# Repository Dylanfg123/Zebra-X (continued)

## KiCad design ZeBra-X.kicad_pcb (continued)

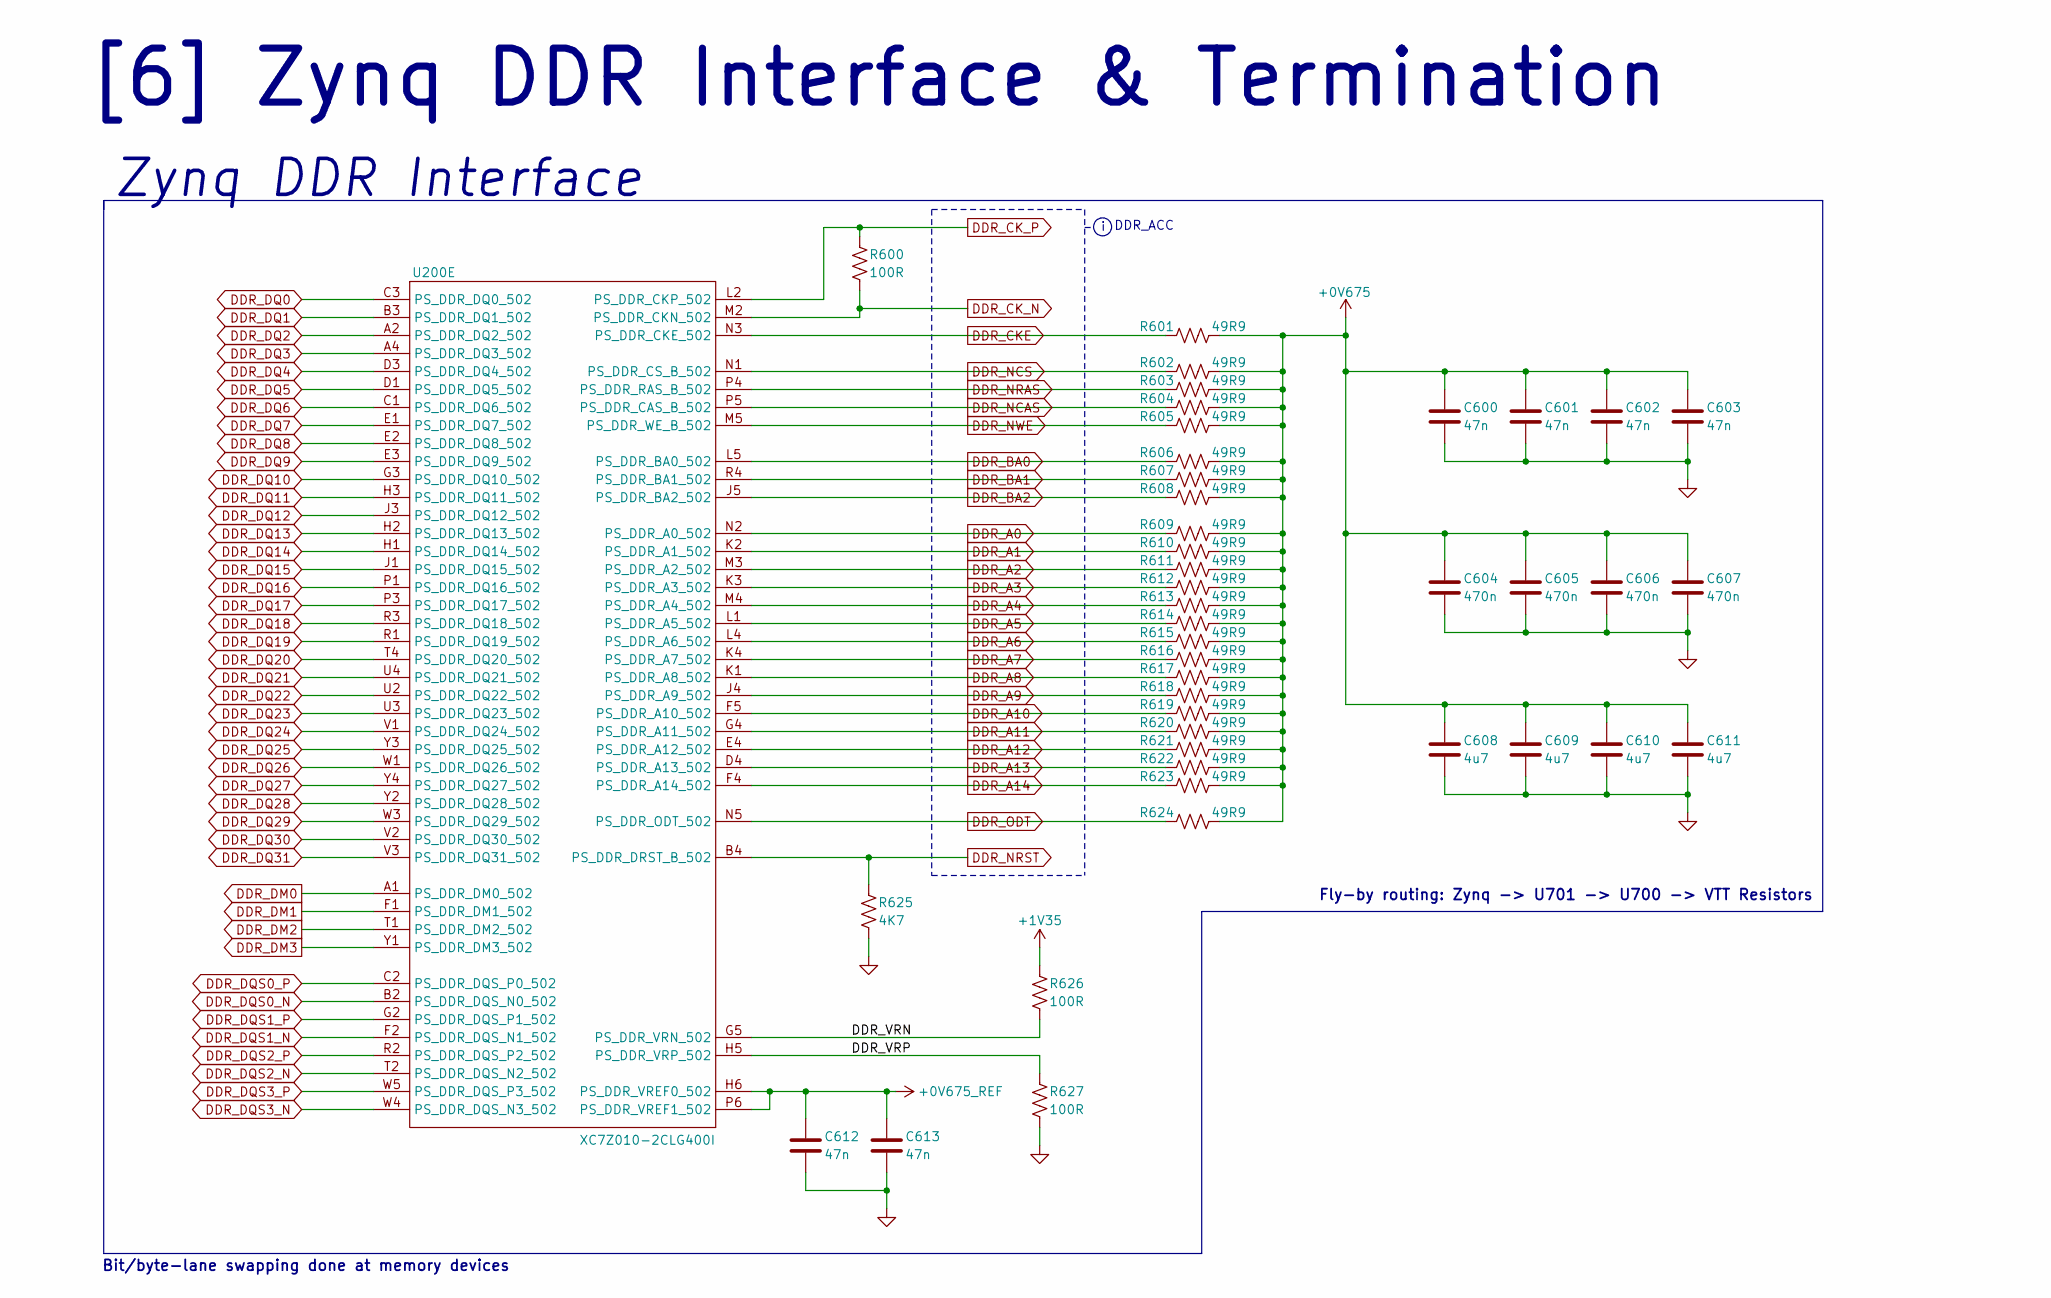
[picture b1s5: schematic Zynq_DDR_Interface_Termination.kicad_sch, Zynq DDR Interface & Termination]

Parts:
C600, C601, C602, C603, C612, C613: 47n; C_0201_0603Metric; Manufacturer PN GRT033R60J473KE01D; LCSC PN C126621
C604, C605, C606, C607: 470n; C_0201_0603Metric; Manufacturer PN GRM033R60J474KE90D; LCSC PN C85926
C608, C609, C610, C611: 4u7; C_0402_1005Metric; Manufacturer PN CL05A475MP5NRNC; LCSC PN C23733
R600, R626, R627: 100R; R_0201_0603Metric; Manufacturer PN RC0201FR-07100RL; LCSC PN C77623
R601, R602, R603, R604, R605, R606, R607, R608, R609, R610, R611, R612, R613, R614, R615, R616, R617, R618, R619, R620, R621, R622, R623, R624: 49R9; R_0201_0603Metric; Manufacturer PN RC0201FR-0749R9L; LCSC PN C155744
R625: 4K7; R_0402_1005Metric; Manufacturer PN RC0402FR-074K7L; LCSC PN C105871
U200: XC7Z010-2CLG400I; CLG400_XIL; Manufacturer PN XC7Z010-2CLG400I; LCSC PN C2840993

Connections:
+0V675: C600.1, C601.1, C602.1, C603.1, C604.1, C605.1, C606.1, C607.1, C608.1, C609.1, C610.1, C611.1, R601.1, R602.1, R603.1, R604.1, R605.1, R606.1, R607.1, R608.1, R609.1, R610.1, R611.1, R612.1, R613.1, R614.1, R615.1, R616.1, R617.1, R618.1, R619.1, R620.1, R621.1, R622.1, R623.1, R624.1; also elsewhere on the board
+0V675_REF: C612.1, C613.1, U200.H6 (PS_DDR_VREF0_502), U200.P6 (PS_DDR_VREF1_502); also elsewhere on the board
+1V35: R626.1; also elsewhere on the board
/[6] Zynq DDR Interface & Termination/DDR_VRN: R626.2, U200.G5 (PS_DDR_VRN_502)
/[6] Zynq DDR Interface & Termination/DDR_VRP: R627.1, U200.H5 (PS_DDR_VRP_502)
DDR_A0: R609.2, U200.N2 (PS_DDR_A0_502); also elsewhere on the board
DDR_A1: R610.2, U200.K2 (PS_DDR_A1_502); also elsewhere on the board
DDR_A2: R611.2, U200.M3 (PS_DDR_A2_502); also elsewhere on the board
DDR_A3: R612.2, U200.K3 (PS_DDR_A3_502); also elsewhere on the board
DDR_A4: R613.2, U200.M4 (PS_DDR_A4_502); also elsewhere on the board
DDR_A5: R614.2, U200.L1 (PS_DDR_A5_502); also elsewhere on the board
DDR_A6: R615.2, U200.L4 (PS_DDR_A6_502); also elsewhere on the board
DDR_A7: R616.2, U200.K4 (PS_DDR_A7_502); also elsewhere on the board
DDR_A8: R617.2, U200.K1 (PS_DDR_A8_502); also elsewhere on the board
DDR_A9: R618.2, U200.J4 (PS_DDR_A9_502); also elsewhere on the board
DDR_A10: R619.2, U200.F5 (PS_DDR_A10_502); also elsewhere on the board
DDR_A11: R620.2, U200.G4 (PS_DDR_A11_502); also elsewhere on the board
DDR_A12: R621.2, U200.E4 (PS_DDR_A12_502); also elsewhere on the board
DDR_A13: R622.2, U200.D4 (PS_DDR_A13_502); also elsewhere on the board
DDR_A14: R623.2, U200.F4 (PS_DDR_A14_502); also elsewhere on the board
DDR_BA0: R606.2, U200.L5 (PS_DDR_BA0_502); also elsewhere on the board
DDR_BA1: R607.2, U200.R4 (PS_DDR_BA1_502); also elsewhere on the board
DDR_BA2: R608.2, U200.J5 (PS_DDR_BA2_502); also elsewhere on the board
DDR_CKE: R601.2, U200.N3 (PS_DDR_CKE_502); also elsewhere on the board
DDR_CK_N: R600.2, U200.M2 (PS_DDR_CKN_502); also elsewhere on the board
DDR_CK_P: R600.1, U200.L2 (PS_DDR_CKP_502); also elsewhere on the board
DDR_DM0: U200.A1 (PS_DDR_DM0_502); also elsewhere on the board
DDR_DM1: U200.F1 (PS_DDR_DM1_502); also elsewhere on the board
DDR_DM2: U200.T1 (PS_DDR_DM2_502); also elsewhere on the board
DDR_DM3: U200.Y1 (PS_DDR_DM3_502); also elsewhere on the board
DDR_DQ0: U200.C3 (PS_DDR_DQ0_502); also elsewhere on the board
DDR_DQ1: U200.B3 (PS_DDR_DQ1_502); also elsewhere on the board
DDR_DQ2: U200.A2 (PS_DDR_DQ2_502); also elsewhere on the board
DDR_DQ3: U200.A4 (PS_DDR_DQ3_502); also elsewhere on the board
DDR_DQ4: U200.D3 (PS_DDR_DQ4_502); also elsewhere on the board
DDR_DQ5: U200.D1 (PS_DDR_DQ5_502); also elsewhere on the board
DDR_DQ6: U200.C1 (PS_DDR_DQ6_502); also elsewhere on the board
DDR_DQ7: U200.E1 (PS_DDR_DQ7_502); also elsewhere on the board
DDR_DQ8: U200.E2 (PS_DDR_DQ8_502); also elsewhere on the board
DDR_DQ9: U200.E3 (PS_DDR_DQ9_502); also elsewhere on the board
DDR_DQ10: U200.G3 (PS_DDR_DQ10_502); also elsewhere on the board
DDR_DQ11: U200.H3 (PS_DDR_DQ11_502); also elsewhere on the board
DDR_DQ12: U200.J3 (PS_DDR_DQ12_502); also elsewhere on the board
DDR_DQ13: U200.H2 (PS_DDR_DQ13_502); also elsewhere on the board
DDR_DQ14: U200.H1 (PS_DDR_DQ14_502); also elsewhere on the board
DDR_DQ15: U200.J1 (PS_DDR_DQ15_502); also elsewhere on the board
DDR_DQ16: U200.P1 (PS_DDR_DQ16_502); also elsewhere on the board
DDR_DQ17: U200.P3 (PS_DDR_DQ17_502); also elsewhere on the board
DDR_DQ18: U200.R3 (PS_DDR_DQ18_502); also elsewhere on the board
DDR_DQ19: U200.R1 (PS_DDR_DQ19_502); also elsewhere on the board
DDR_DQ20: U200.T4 (PS_DDR_DQ20_502); also elsewhere on the board
DDR_DQ21: U200.U4 (PS_DDR_DQ21_502); also elsewhere on the board
DDR_DQ22: U200.U2 (PS_DDR_DQ22_502); also elsewhere on the board
DDR_DQ23: U200.U3 (PS_DDR_DQ23_502); also elsewhere on the board
DDR_DQ24: U200.V1 (PS_DDR_DQ24_502); also elsewhere on the board
DDR_DQ25: U200.Y3 (PS_DDR_DQ25_502); also elsewhere on the board
DDR_DQ26: U200.W1 (PS_DDR_DQ26_502); also elsewhere on the board
DDR_DQ27: U200.Y4 (PS_DDR_DQ27_502); also elsewhere on the board
DDR_DQ28: U200.Y2 (PS_DDR_DQ28_502); also elsewhere on the board
DDR_DQ29: U200.W3 (PS_DDR_DQ29_502); also elsewhere on the board
DDR_DQ30: U200.V2 (PS_DDR_DQ30_502); also elsewhere on the board
DDR_DQ31: U200.V3 (PS_DDR_DQ31_502); also elsewhere on the board
DDR_DQS0_N: U200.B2 (PS_DDR_DQS_N0_502); also elsewhere on the board
DDR_DQS0_P: U200.C2 (PS_DDR_DQS_P0_502); also elsewhere on the board
DDR_DQS1_N: U200.F2 (PS_DDR_DQS_N1_502); also elsewhere on the board
DDR_DQS1_P: U200.G2 (PS_DDR_DQS_P1_502); also elsewhere on the board
DDR_DQS2_N: U200.T2 (PS_DDR_DQS_N2_502); also elsewhere on the board
DDR_DQS2_P: U200.R2 (PS_DDR_DQS_P2_502); also elsewhere on the board
DDR_DQS3_N: U200.W4 (PS_DDR_DQS_N3_502); also elsewhere on the board
DDR_DQS3_P: U200.W5 (PS_DDR_DQS_P3_502); also elsewhere on the board
DDR_NCAS: R604.2, U200.P5 (PS_DDR_CAS_B_502); also elsewhere on the board
DDR_NCS: R602.2, U200.N1 (PS_DDR_CS_B_502); also elsewhere on the board
DDR_NRAS: R603.2, U200.P4 (PS_DDR_RAS_B_502); also elsewhere on the board
DDR_NRST: R625.1, U200.B4 (PS_DDR_DRST_B_502); also elsewhere on the board
DDR_NWE: R605.2, U200.M5 (PS_DDR_WE_B_502); also elsewhere on the board
DDR_ODT: R624.2, U200.N5 (PS_DDR_ODT_502); also elsewhere on the board
GND: C600.2, C601.2, C602.2, C603.2, C604.2, C605.2, C606.2, C607.2, C608.2, C609.2, C610.2, C611.2, C612.2, C613.2, R625.2, R627.2; also elsewhere on the board

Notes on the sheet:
Bit/byte-lane swapping done at memory devices
Zynq DDR Interface
DDR_ACC
[6] Zynq DDR Interface & Termination
Fly-by routing: Zynq -> U701 -> U700 -> VTT Resistors

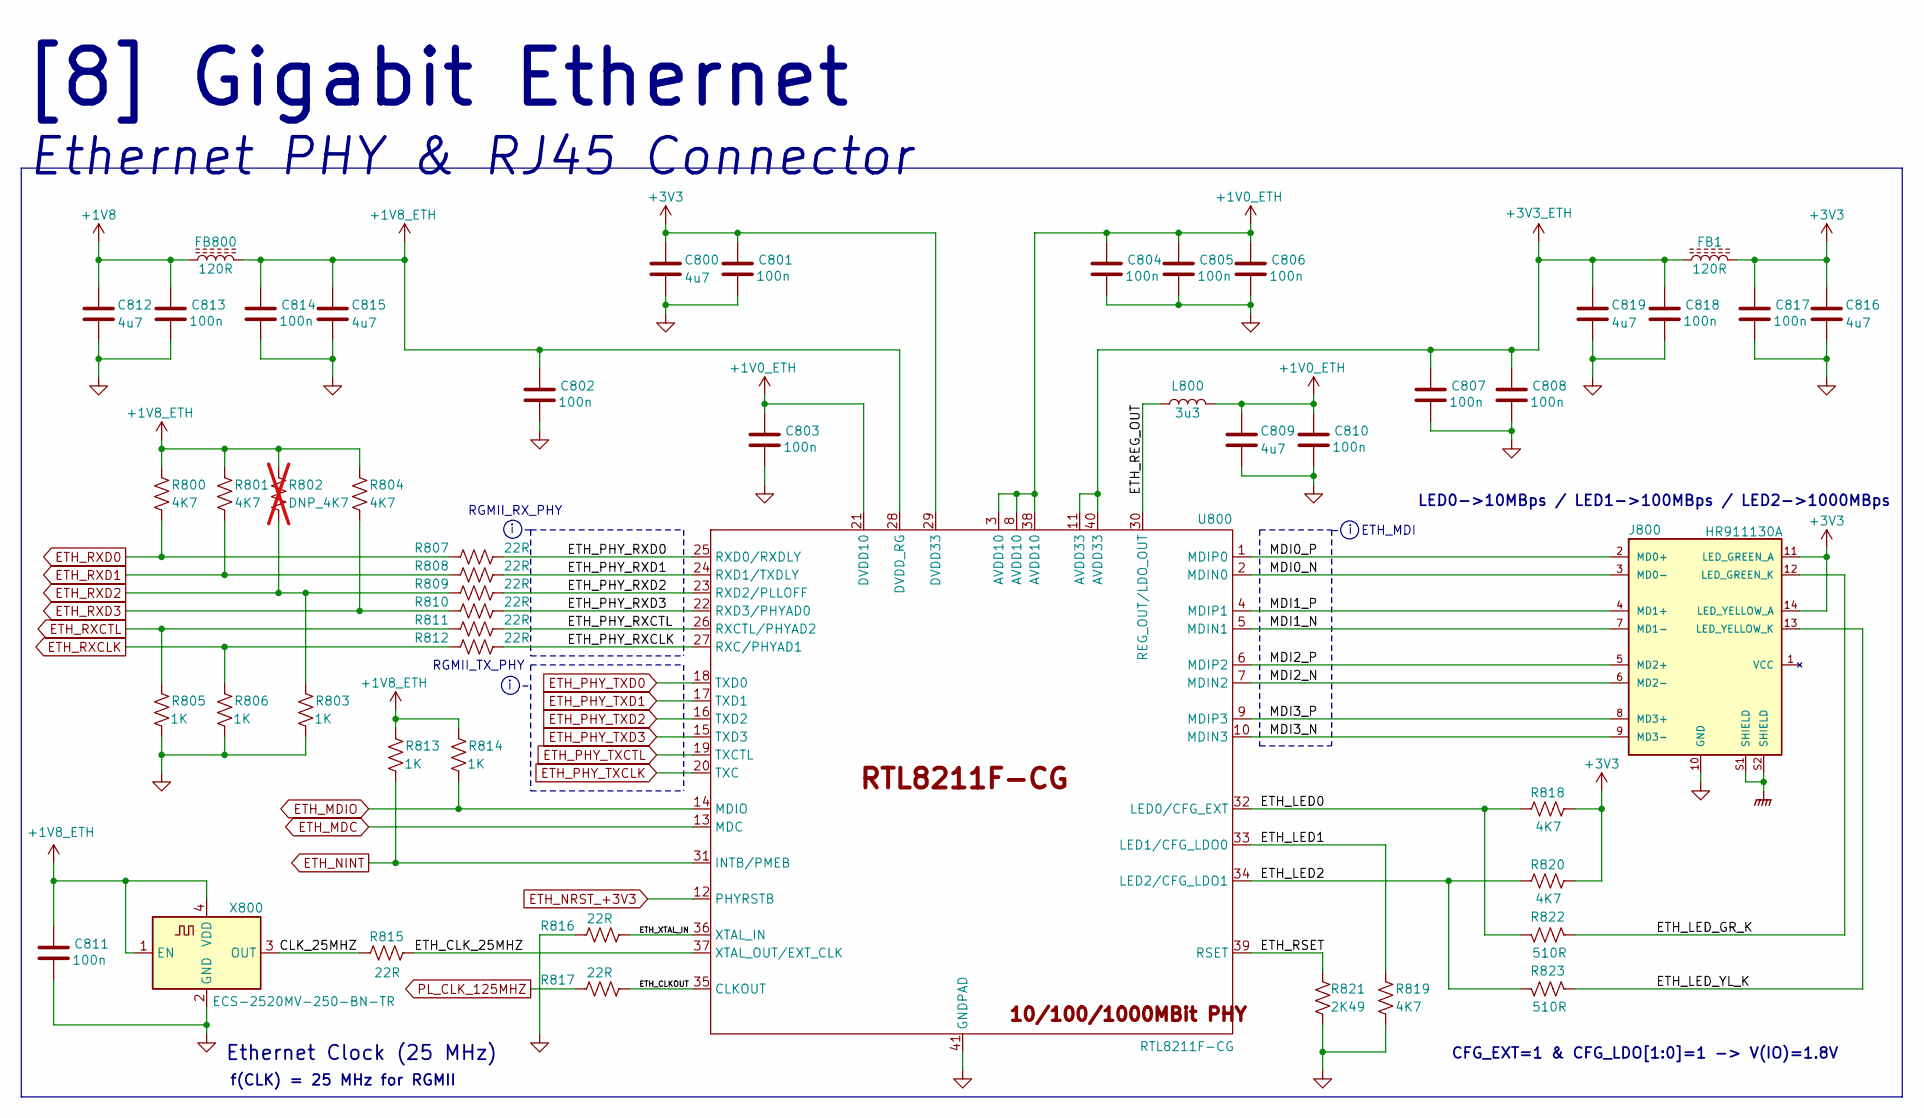
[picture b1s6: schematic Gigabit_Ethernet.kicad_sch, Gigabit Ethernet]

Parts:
C800, C809, C812, C815, C816, C819: 4u7; C_0402_1005Metric; Manufacturer PN CL05A475MP5NRNC; LCSC PN C23733
C801, C802, C803, C804, C805, C806, C807, C808, C810, C811, C813, C814, C817, C818: 100n; C_0402_1005Metric; Manufacturer PN CC0402KRX5R8BB104; LCSC PN C106256
FB1, FB800: 120R; L_0402_1005Metric; Manufacturer PN BLM15PX121SN1D; LCSC PN C88970
J800: HR911130A; HANRUN_HR911130A; Manufacturer PN HR911130A
L800: 3u3; L_0603_1608Metric; Manufacturer PN LQM18PN3R3MGHD
R800, R801, R804, R818, R819, R820: 4K7; R_0402_1005Metric; Manufacturer PN RC0402FR-074K7L; LCSC PN C105871
R802: DNP_4K7; R_0402_1005Metric; Manufacturer PN RC0402FR-074K7L; LCSC PN C105871; not fitted
R803, R805, R806, R813, R814: 1K; R_0402_1005Metric; Manufacturer PN RC0402FR-071KL; LCSC PN C106235
R807, R808, R809, R810, R811, R812, R815, R816, R817: 22R; R_0402_1005Metric; Manufacturer PN RC0402FR-0722RL; LCSC PN C114765
R821: 2K49; R_0402_1005Metric; Manufacturer PN RC0402FR-072K49L; LCSC PN C145071
R822, R823: 510R; R_0402_1005Metric; Manufacturer PN RC0402FR-07510RL; LCSC PN C276273
U800: RTL8211F-CG; QFN-40-1EP_5x5mm_P0.4mm_EP3.8x3.8mm; Manufacturer PN RTL8211F-CG; LCSC PN C187932
X800: ECS-2520MV-250-BN-TR; Oscillator_SMD_ECS_2520MV-xxx-xx-4Pin_2.5x2.0mm; Manufacturer PN ECS-2520MV-250-BN-TR

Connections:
+1V0_ETH: C803.1, C804.1, C805.1, C806.1, C809.1, C810.1, L800.2, U800.3 (AVDD10), U800.8 (AVDD10), U800.21 (DVDD10), U800.38 (AVDD10)
+1V8: C812.1, C813.1, FB800.1; also elsewhere on the board
+1V8_ETH: C802.1, C811.1, C814.1, C815.1, FB800.2, R800.1, R801.1, R802.1, R804.1, R813.2, R814.2, U800.28 (DVDD_RG), X800.1 (EN), X800.4 (VDD)
+3V3: C800.1, C801.1, C816.1, C817.1, FB1.2, J800.11 (LED_GREEN_A), J800.14 (LED_YELLOW_A), R818.2, R820.2, U800.29 (DVDD33); also elsewhere on the board
+3V3_ETH: C807.1, C808.1, C818.1, C819.1, FB1.1, U800.11 (AVDD33), U800.40 (AVDD33)
/[8] Gigabit Ethernet/CLK_25MHZ: R815.1, X800.3 (OUT)
/[8] Gigabit Ethernet/ETH_CLKOUT: R817.2, U800.35 (CLKOUT)
/[8] Gigabit Ethernet/ETH_CLK_25MHZ: R815.2, U800.37 (XTAL_OUT/EXT_CLK)
/[8] Gigabit Ethernet/ETH_LED0: R818.1, R822.2, U800.32 (LED0/CFG_EXT)
/[8] Gigabit Ethernet/ETH_LED1: R819.1, U800.33 (LED1/CFG_LDO0)
/[8] Gigabit Ethernet/ETH_LED2: R820.1, R823.2, U800.34 (LED2/CFG_LDO1)
/[8] Gigabit Ethernet/ETH_LED_GR_K: J800.12 (LED_GREEN_K), R822.1
/[8] Gigabit Ethernet/ETH_LED_YL_K: J800.13 (LED_YELLOW_K), R823.1
/[8] Gigabit Ethernet/ETH_PHY_RXCLK: R812.2, U800.27 (RXC/PHYAD1)
/[8] Gigabit Ethernet/ETH_PHY_RXCTL: R811.2, U800.26 (RXCTL/PHYAD2)
/[8] Gigabit Ethernet/ETH_PHY_RXD0: R807.2, U800.25 (RXD0/RXDLY)
/[8] Gigabit Ethernet/ETH_PHY_RXD1: R808.2, U800.24 (RXD1/TXDLY)
/[8] Gigabit Ethernet/ETH_PHY_RXD2: R809.2, U800.23 (RXD2/PLLOFF)
/[8] Gigabit Ethernet/ETH_PHY_RXD3: R810.2, U800.22 (RXD3/PHYAD0)
/[8] Gigabit Ethernet/ETH_REG_OUT: L800.1, U800.30 (REG_OUT/LDO_OUT)
/[8] Gigabit Ethernet/ETH_RSET: R821.1, U800.39 (RSET)
/[8] Gigabit Ethernet/ETH_XTAL_IN: R816.2, U800.36 (XTAL_IN)
/[8] Gigabit Ethernet/MDI0_N: J800.3 (MD0-), U800.2 (MDIN0)
/[8] Gigabit Ethernet/MDI0_P: J800.2 (MD0+), U800.1 (MDIP0)
/[8] Gigabit Ethernet/MDI1_N: J800.7 (MD1-), U800.5 (MDIN1)
/[8] Gigabit Ethernet/MDI1_P: J800.4 (MD1+), U800.4 (MDIP1)
/[8] Gigabit Ethernet/MDI2_N: J800.6 (MD2-), U800.7 (MDIN2)
/[8] Gigabit Ethernet/MDI2_P: J800.5 (MD2+), U800.6 (MDIP2)
/[8] Gigabit Ethernet/MDI3_N: J800.9 (MD3-), U800.10 (MDIN3)
/[8] Gigabit Ethernet/MDI3_P: J800.8 (MD3+), U800.9 (MDIP3)
ETH_MDC: U800.13 (MDC); also elsewhere on the board
ETH_MDIO: R814.1, U800.14 (MDIO); also elsewhere on the board
ETH_NINT: R813.1, U800.31 (INTB/PMEB); also elsewhere on the board
ETH_NRST_+3V3: U800.12 (PHYRSTB); also elsewhere on the board
ETH_PHY_TXCLK: U800.20 (TXC); also elsewhere on the board
ETH_PHY_TXCTL: U800.19 (TXCTL); also elsewhere on the board
ETH_PHY_TXD0: U800.18 (TXD0); also elsewhere on the board
ETH_PHY_TXD1: U800.17 (TXD1); also elsewhere on the board
ETH_PHY_TXD2: U800.16 (TXD2); also elsewhere on the board
ETH_PHY_TXD3: U800.15 (TXD3); also elsewhere on the board
ETH_RXCLK: R806.2, R812.1; also elsewhere on the board
ETH_RXCTL: R805.2, R811.1; also elsewhere on the board
ETH_RXD0: R800.2, R807.1; also elsewhere on the board
ETH_RXD1: R801.2, R808.1; also elsewhere on the board
ETH_RXD2: R802.2, R803.2, R809.1; also elsewhere on the board
ETH_RXD3: R804.2, R810.1; also elsewhere on the board
GND: C800.2, C801.2, C802.2, C803.2, C804.2, C805.2, C806.2, C807.2, C808.2, C809.2, C810.2, C811.2, C812.2, C813.2, C814.2, C815.2, C816.2, C817.2, C818.2, C819.2, J800.10 (GND), R803.1, R805.1, R806.1, R816.1, R819.2, R821.2, U800.41 (GNDPAD), X800.2 (GND); also elsewhere on the board
GNDPWR: J800.S1 (SHIELD), J800.S2 (SHIELD); also elsewhere on the board
PL_CLK_125MHZ: R817.1; also elsewhere on the board

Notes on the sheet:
RGMII_TX_PHY
Ethernet PHY & RJ45 Connector
[8] Gigabit Ethernet
RGMII_RX_PHY
Ethernet Clock (25 MHz)
LED0->10MBps / LED1->100MBps / LED2->1000MBps
f(CLK) = 25 MHz for RGMII
CFG_EXT=1 & CFG_LDO[1:0]=1 -> V(IO)=1.8V
ETH_MDI

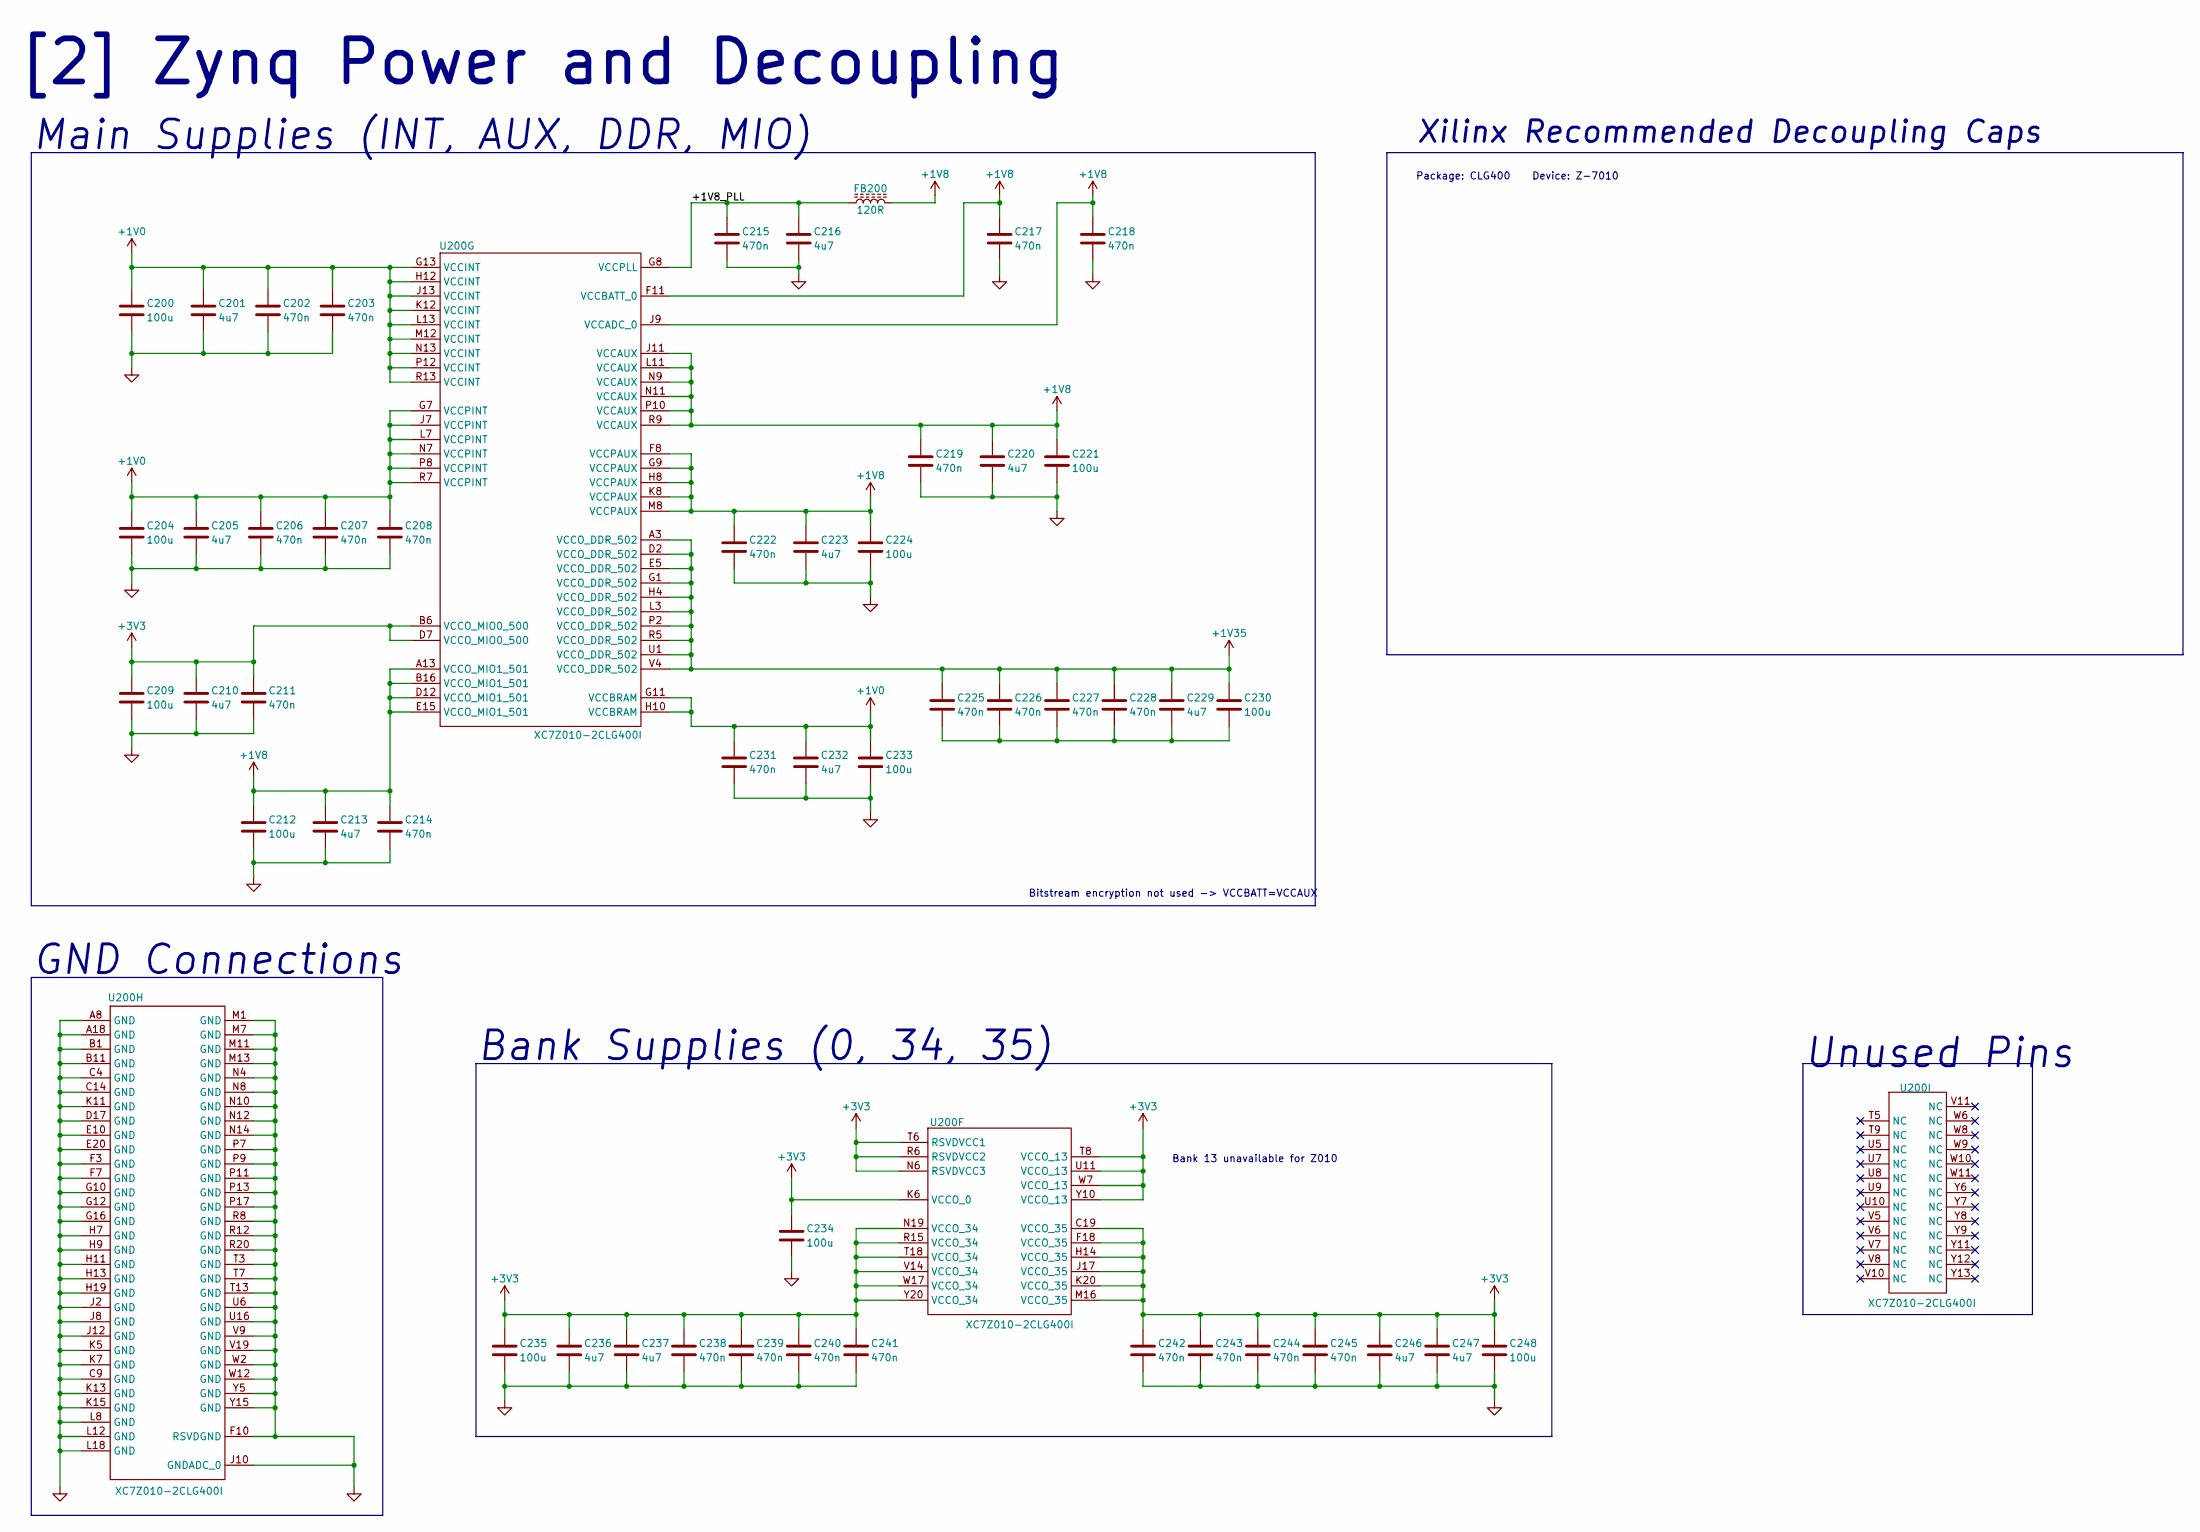
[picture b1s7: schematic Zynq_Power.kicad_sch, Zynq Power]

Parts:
C200, C204, C209, C212, C221, C224, C230, C233, C234, C235, C248: 100u; C_1210_3225Metric; Manufacturer PN CL32A107MQVNNNE; LCSC PN C49066
C201, C205, C210, C213, C216, C220, C223, C229, C232, C236, C237, C246, C247: 4u7; C_0402_1005Metric; Manufacturer PN CL05A475MP5NRNC; LCSC PN C23733
C202, C203, C206, C207, C208, C211, C214, C215, C217, C218, C219, C222, C225, C226, C227, C228, C231, C238, C239, C240, C241, C242, C243, C244, C245: 470n; C_0201_0603Metric; Manufacturer PN GRM033R60J474KE90D; LCSC PN C85926
FB200: 120R; L_0402_1005Metric; Manufacturer PN BLM15PX121SN1D; LCSC PN C88970
U200: XC7Z010-2CLG400I; CLG400_XIL; Manufacturer PN XC7Z010-2CLG400I; LCSC PN C2840993

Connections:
+1V0: C200.1, C201.1, C202.1, C203.1, C204.1, C205.1, C206.1, C207.1, C208.1, C231.1, C232.1, C233.1, U200.G7 (VCCPINT), U200.G11 (VCCBRAM), U200.G13 (VCCINT), U200.H10 (VCCBRAM), U200.H12 (VCCINT), U200.J7 (VCCPINT), U200.J13 (VCCINT), U200.K12 (VCCINT), U200.L7 (VCCPINT), U200.L13 (VCCINT), U200.M12 (VCCINT), U200.N7 (VCCPINT), U200.N13 (VCCINT), U200.P8 (VCCPINT), U200.P12 (VCCINT), U200.R7 (VCCPINT), U200.R13 (VCCINT); also elsewhere on the board
+1V8: C212.1, C213.1, C214.1, C217.1, C218.1, C219.1, C220.1, C221.1, C222.1, C223.1, C224.1, FB200.2, U200.A13 (VCCO_MIO1_501), U200.B16 (VCCO_MIO1_501), U200.D12 (VCCO_MIO1_501), U200.E15 (VCCO_MIO1_501), U200.F8 (VCCPAUX), U200.F11 (VCCBATT_0), U200.G9 (VCCPAUX), U200.H8 (VCCPAUX), U200.J9 (VCCADC_0), U200.J11 (VCCAUX), U200.K8 (VCCPAUX), U200.L11 (VCCAUX), U200.M8 (VCCPAUX), U200.N9 (VCCAUX), U200.N11 (VCCAUX), U200.P10 (VCCAUX), U200.R9 (VCCAUX); also elsewhere on the board
+1V35: C225.1, C226.1, C227.1, C228.1, C229.1, C230.1, U200.A3 (VCCO_DDR_502), U200.D2 (VCCO_DDR_502), U200.E5 (VCCO_DDR_502), U200.G1 (VCCO_DDR_502), U200.H4 (VCCO_DDR_502), U200.L3 (VCCO_DDR_502), U200.P2 (VCCO_DDR_502), U200.R5 (VCCO_DDR_502), U200.U1 (VCCO_DDR_502), U200.V4 (VCCO_DDR_502); also elsewhere on the board
+3V3: C209.1, C210.1, C211.1, C234.1, C235.1, C236.1, C237.1, C238.1, C239.1, C240.1, C241.1, C242.1, C243.1, C244.1, C245.1, C246.1, C247.1, C248.1, U200.B6 (VCCO_MIO0_500), U200.C19 (VCCO_35), U200.D7 (VCCO_MIO0_500), U200.F18 (VCCO_35), U200.H14 (VCCO_35), U200.J17 (VCCO_35), U200.K6 (VCCO_0), U200.K20 (VCCO_35), U200.M16 (VCCO_35), U200.N6 (RSVDVCC3), U200.N19 (VCCO_34), U200.R6 (RSVDVCC2), U200.R15 (VCCO_34), U200.T6 (RSVDVCC1), U200.T8 (VCCO_13), U200.T18 (VCCO_34), U200.U11 (VCCO_13), U200.V14 (VCCO_34), U200.W7 (VCCO_13), U200.W17 (VCCO_34), U200.Y10 (VCCO_13), U200.Y20 (VCCO_34); also elsewhere on the board
/[2] Zynq Power/+1V8_PLL: C215.1, C216.1, FB200.1, U200.G8 (VCCPLL)
GND: C200.2, C201.2, C202.2, C203.2, C204.2, C205.2, C206.2, C207.2, C208.2, C209.2, C210.2, C211.2, C212.2, C213.2, C214.2, C215.2, C216.2, C217.2, C218.2, C219.2, C220.2, C221.2, C222.2, C223.2, C224.2, C231.2, C232.2, C233.2, C234.2, C235.2, C236.2, C237.2, C238.2, C239.2, C240.2, C241.2, C242.2, C243.2, C244.2, C245.2, C246.2, C247.2, C248.2, U200.A8 (GND), U200.A18 (GND), U200.B1 (GND), U200.B11 (GND), U200.C4 (GND), U200.C9 (GND), U200.C14 (GND), U200.D17 (GND), U200.E10 (GND), U200.E20 (GND), U200.F3 (GND), U200.F7 (GND), U200.F10 (RSVDGND), U200.G10 (GND), U200.G12 (GND), U200.G16 (GND), U200.H7 (GND), U200.H9 (GND), U200.H11 (GND), U200.H13 (GND), U200.H19 (GND), U200.J2 (GND), U200.J8 (GND), U200.J10 (GNDADC_0), U200.J12 (GND), U200.K5 (GND), U200.K7 (GND), U200.K11 (GND), U200.K13 (GND), U200.K15 (GND), U200.L8 (GND), U200.L12 (GND), U200.L18 (GND), U200.M1 (GND), U200.M7 (GND), U200.M11 (GND), U200.M13 (GND), U200.N4 (GND), U200.N8 (GND), U200.N10 (GND), U200.N12 (GND), U200.N14 (GND), U200.P7 (GND), U200.P9 (GND), U200.P11 (GND), U200.P13 (GND), U200.P17 (GND), U200.R8 (GND), U200.R12 (GND), U200.R20 (GND), U200.T3 (GND), U200.T7 (GND), U200.T13 (GND), U200.U6 (GND), U200.U16 (GND), U200.V9 (GND), U200.V19 (GND), U200.W2 (GND), U200.W12 (GND), U200.Y5 (GND), U200.Y15 (GND); also elsewhere on the board
unnamed: C225.2, C226.2, C227.2, C228.2, C229.2, C230.2

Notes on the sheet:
Main Supplies (INT, AUX, DDR, MIO)
Bank Supplies (0, 34, 35)
Unused Pins
Xilinx Recommended Decoupling Caps
[2] Zynq Power and Decoupling
Package: CLG400 Device: Z-7010
Bank 13 unavailable for Z010
Bitstream encryption not used -> VCCBATT=VCCAUX
GND Connections

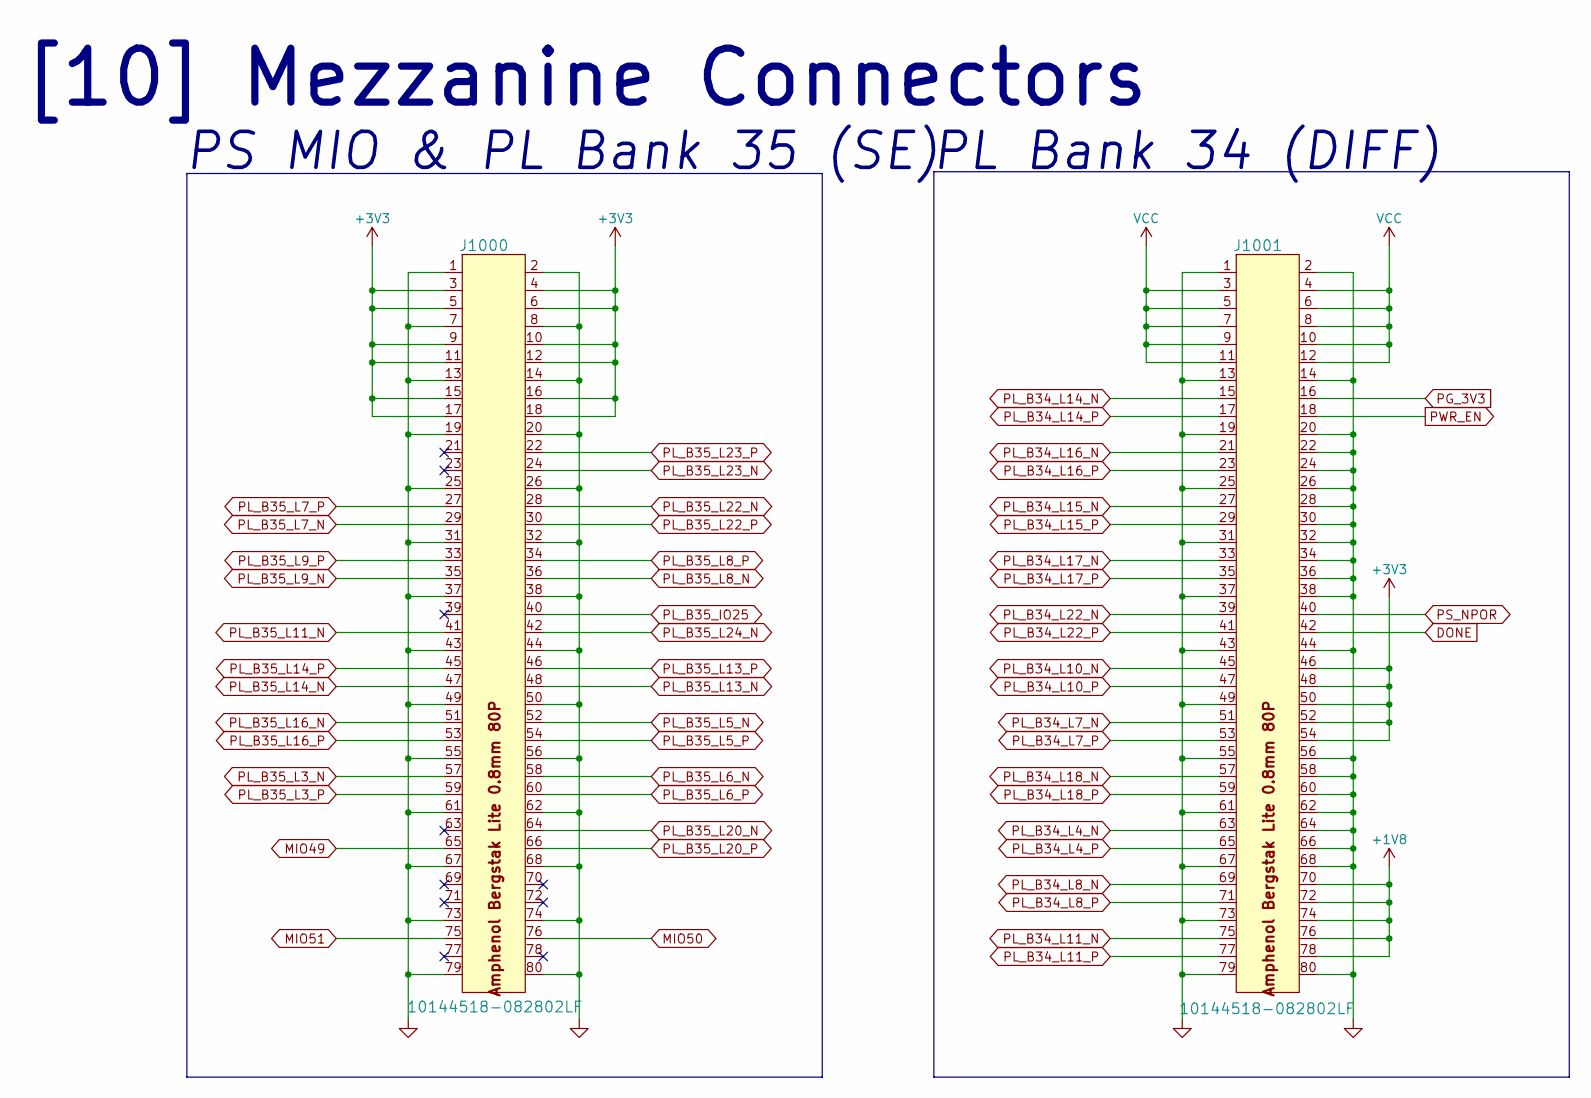
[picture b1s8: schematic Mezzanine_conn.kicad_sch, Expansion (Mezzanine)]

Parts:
J1000, J1001: 10144518-082802LF; CONN_10144518_AMP; Manufacturer PN 10144518-082802LF

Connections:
+1V8: J1001.70, J1001.72, J1001.74, J1001.76, J1001.78; also elsewhere on the board
+3V3: J1000.3, J1000.4, J1000.5, J1000.6, J1000.9, J1000.10, J1000.11, J1000.12, J1000.15, J1000.16, J1000.17, J1000.18, J1001.46, J1001.48, J1001.50, J1001.52, J1001.54; also elsewhere on the board
DONE: J1001.42; also elsewhere on the board
GND: J1000.1, J1000.2, J1000.7, J1000.8, J1000.13, J1000.14, J1000.19, J1000.20, J1000.25, J1000.26, J1000.31, J1000.32, J1000.37, J1000.38, J1000.43, J1000.44, J1000.49, J1000.50, J1000.55, J1000.56, J1000.61, J1000.62, J1000.67, J1000.68, J1000.73, J1000.74, J1000.79, J1000.80, J1001.1, J1001.2, J1001.13, J1001.14, J1001.19, J1001.20, J1001.22, J1001.24, J1001.25, J1001.26, J1001.28, J1001.30, J1001.31, J1001.32, J1001.34, J1001.36, J1001.37, J1001.38, J1001.43, J1001.44, J1001.49, J1001.55, J1001.56, J1001.58, J1001.60, J1001.61, J1001.62, J1001.64, J1001.66, J1001.67, J1001.68, J1001.73, J1001.79, J1001.80; also elsewhere on the board
MIO49: J1000.65; also elsewhere on the board
MIO50: J1000.76; also elsewhere on the board
MIO51: J1000.75; also elsewhere on the board
PG_3V3: J1001.16; also elsewhere on the board
PL_B34_L4_N: J1001.63; also elsewhere on the board
PL_B34_L4_P: J1001.65; also elsewhere on the board
PL_B34_L7_N: J1001.51; also elsewhere on the board
PL_B34_L7_P: J1001.53; also elsewhere on the board
PL_B34_L8_N: J1001.69; also elsewhere on the board
PL_B34_L8_P: J1001.71; also elsewhere on the board
PL_B34_L10_N: J1001.45; also elsewhere on the board
PL_B34_L10_P: J1001.47; also elsewhere on the board
PL_B34_L11_N: J1001.75; also elsewhere on the board
PL_B34_L11_P: J1001.77; also elsewhere on the board
PL_B34_L14_N: J1001.15; also elsewhere on the board
PL_B34_L14_P: J1001.17; also elsewhere on the board
PL_B34_L15_N: J1001.27; also elsewhere on the board
PL_B34_L15_P: J1001.29; also elsewhere on the board
PL_B34_L16_N: J1001.21; also elsewhere on the board
PL_B34_L16_P: J1001.23; also elsewhere on the board
PL_B34_L17_N: J1001.33; also elsewhere on the board
PL_B34_L17_P: J1001.35; also elsewhere on the board
PL_B34_L18_N: J1001.57; also elsewhere on the board
PL_B34_L18_P: J1001.59; also elsewhere on the board
PL_B34_L22_N: J1001.39; also elsewhere on the board
PL_B34_L22_P: J1001.41; also elsewhere on the board
PL_B35_IO25: J1000.40; also elsewhere on the board
PL_B35_L3_N: J1000.57; also elsewhere on the board
PL_B35_L3_P: J1000.59; also elsewhere on the board
PL_B35_L5_N: J1000.52; also elsewhere on the board
PL_B35_L5_P: J1000.54; also elsewhere on the board
PL_B35_L6_N: J1000.58; also elsewhere on the board
PL_B35_L6_P: J1000.60; also elsewhere on the board
PL_B35_L7_N: J1000.29; also elsewhere on the board
PL_B35_L7_P: J1000.27; also elsewhere on the board
PL_B35_L8_N: J1000.36; also elsewhere on the board
PL_B35_L8_P: J1000.34; also elsewhere on the board
PL_B35_L9_N: J1000.35; also elsewhere on the board
PL_B35_L9_P: J1000.33; also elsewhere on the board
PL_B35_L11_N: J1000.41; also elsewhere on the board
PL_B35_L13_N: J1000.48; also elsewhere on the board
PL_B35_L13_P: J1000.46; also elsewhere on the board
PL_B35_L14_N: J1000.47; also elsewhere on the board
PL_B35_L14_P: J1000.45; also elsewhere on the board
PL_B35_L16_N: J1000.51; also elsewhere on the board
PL_B35_L16_P: J1000.53; also elsewhere on the board
PL_B35_L20_N: J1000.64; also elsewhere on the board
PL_B35_L20_P: J1000.66; also elsewhere on the board
PL_B35_L22_N: J1000.28; also elsewhere on the board
PL_B35_L22_P: J1000.30; also elsewhere on the board
PL_B35_L23_N: J1000.24; also elsewhere on the board
PL_B35_L23_P: J1000.22; also elsewhere on the board
PL_B35_L24_N: J1000.42; also elsewhere on the board
PS_NPOR: J1001.40; also elsewhere on the board
PWR_EN: J1001.18; also elsewhere on the board
VCC: J1001.3, J1001.4, J1001.5, J1001.6, J1001.7, J1001.8, J1001.9, J1001.10, J1001.11, J1001.12; also elsewhere on the board

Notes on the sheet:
PL Bank 34 (DIFF)
[10] Mezzanine Connectors
PS MIO & PL Bank 35 (SE)
